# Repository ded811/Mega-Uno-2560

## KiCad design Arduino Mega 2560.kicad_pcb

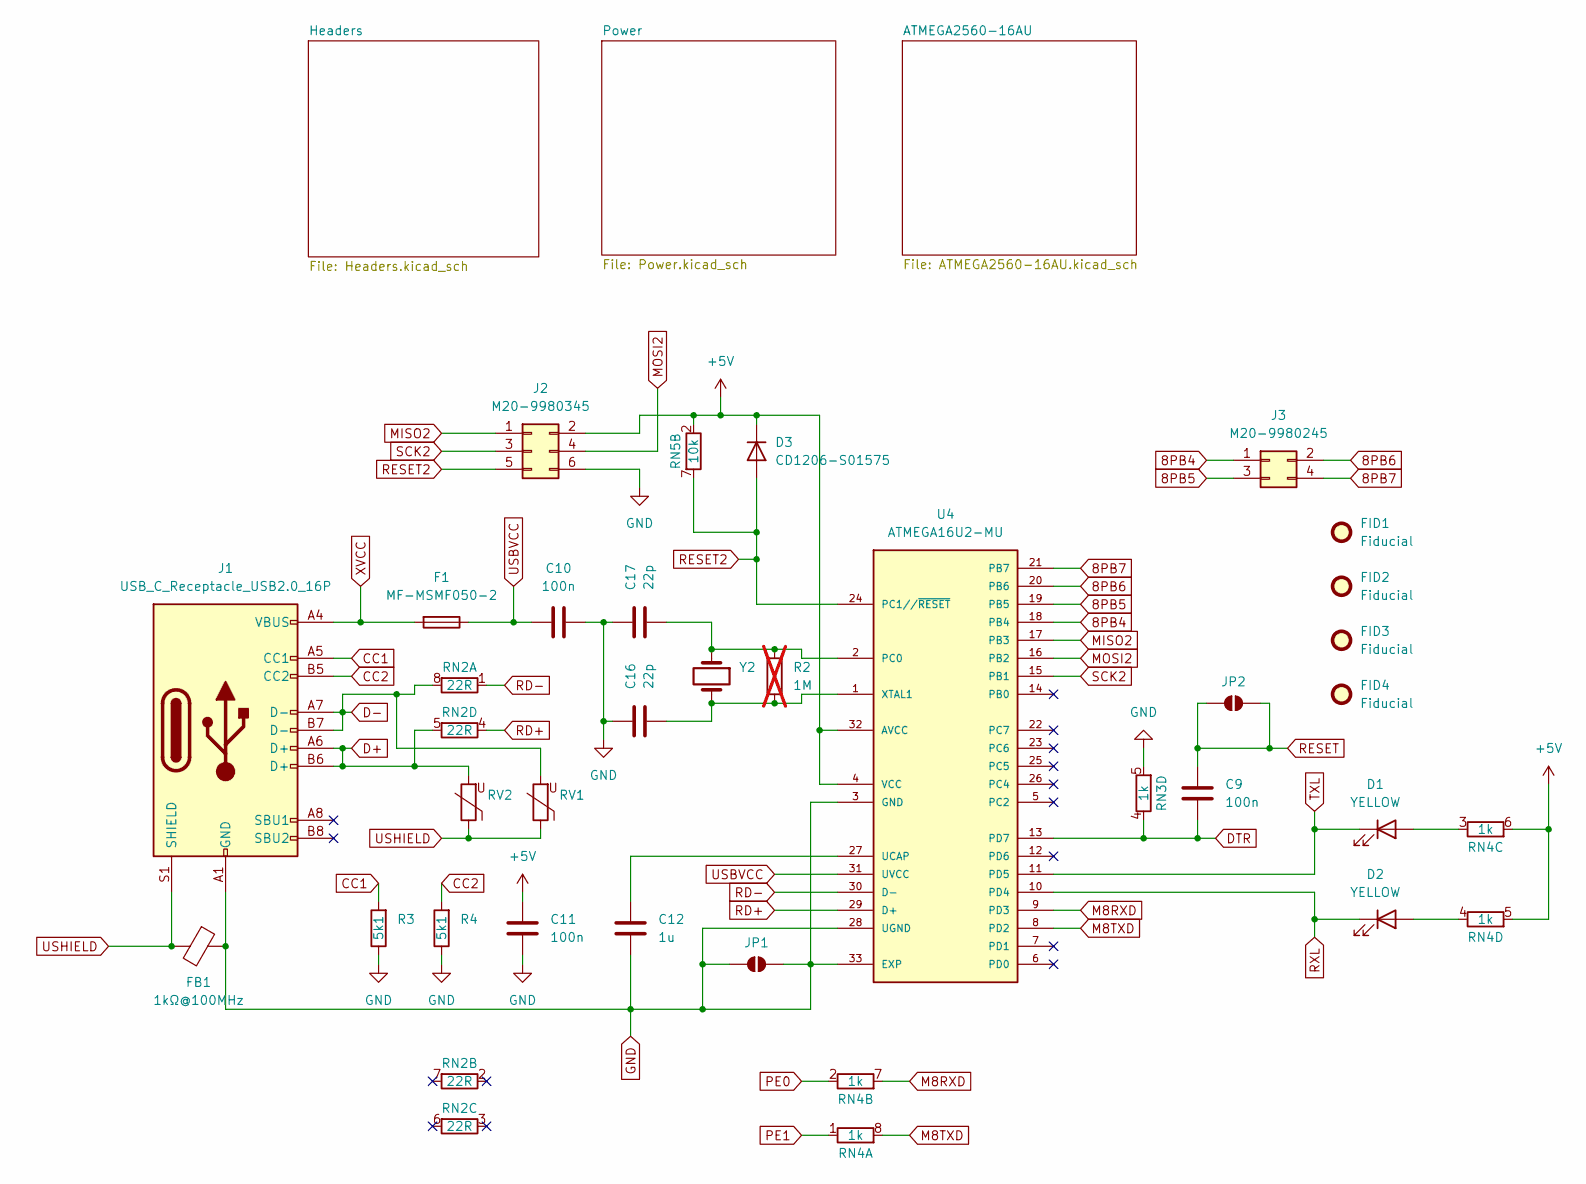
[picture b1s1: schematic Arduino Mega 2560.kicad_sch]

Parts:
C9, C10, C11: 100n; C_0603_1608Metric
C12: 1u; C_0603_1608Metric
C16, C17: 22p; C_0603_1608Metric
D1, D2: YELLOW; LED_0805_2012Metric
D3: CD1206-S01575; D_1206_3216Metric
F1: MF-MSMF050-2; Fuse_1812_4532Metric_Pad1.30x3.40mm_HandSolder
FB1: 1kΩ@100MHz; L_0805_2012Metric
FID1, FID2, FID3, FID4: Fiducial; Fiducial_1mm_Mask3mm
J1: USB_C_Receptacle_USB2.0_16P; USB_C_Receptacle_GCT_USB4105-xx-A_16P_TopMnt_Horizontal
J2: M20-9980345; PinHeader_2x03_P2.54mm_Vertical
J3: M20-9980245; CONN_M20-9980245_HRW
JP1, JP2: SolderJumper_2_Open; SolderJumper-2_P1.3mm_Open_Pad1.0x1.5mm
R2: 1M; R_0603_1608Metric; not fitted
R3, R4: 5k1; R_0603_1608Metric
RN2: 22R; R_Array_Convex_4x0612
RN3, RN4: 1k; R_Array_Convex_4x0612
RN5: 10k; R_Array_Convex_4x0612
RV1, RV2: 5pF@1MHz; R_0603_1608Metric
U4: ATMEGA16U2-MU; VQFN-32-1EP_5x5mm_P0.5mm_EP3.1x3.1mm
Y2: LFXTAL003240BULK; Crystal_HC49-4H_Vertical

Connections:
8PB4: J3.1, U4.18 (PB4)
8PB5: J3.3, U4.19 (PB5)
8PB6: J3.2, U4.20 (PB6)
8PB7: J3.4, U4.21 (PB7)
+5V: C11.1, D3.1 (K), J2.2, RN4.5 (R4.2), RN4.6 (R3.2), RN5.2 (R2.1), U4.4 (VCC), U4.32 (AVCC); also elsewhere on the board
CC1: J1.A5 (CC1), R3.2
CC2: J1.B5 (CC2), R4.2
D+: J1.A6 (D+), J1.B6 (D+), RN2.5 (R4.2), RV2.2
D-: J1.A7 (D-), J1.B7 (D-), RN2.8 (R1.2), RV1.2
DTR: C9.1, RN3.4 (R4.1), U4.13 (PD7)
GND: C10.2, C11.2, C12.2, C16.2, C17.2, FB1.1, J1.A1 (GND), J1.A12 (GND), J1.B1 (GND), J1.B12 (GND), J2.6, JP1.1 (A), JP1.2 (B), R3.1, R4.1, RN3.5 (R4.2), U4.3 (GND), U4.28 (UGND), U4.33 (EXP); also elsewhere on the board
M8RXD: RN4.7 (R2.2), U4.9 (PD3)
M8TXD: RN4.8 (R1.2), U4.8 (PD2)
MISO2: J2.1, U4.17 (PB3)
MOSI2: J2.4, U4.16 (PB2)
unnamed: D1.2 (A), RN4.3 (R3.1)
unnamed: D2.2 (A), RN4.4 (R4.1)
unnamed: C17.1, R2.2, U4.2 (PC0), Y2.1
unnamed: C12.1, U4.27 (UCAP)
unnamed: C16.1, R2.1, U4.1 (XTAL1), Y2.2
PE0: RN4.2 (R2.1); also elsewhere on the board
PE1: RN4.1 (R1.1); also elsewhere on the board
RD+: RN2.4 (R4.1), U4.29 (D+)
RD-: RN2.1 (R1.1), U4.30 (D-)
RESET: C9.2, JP2.1 (A), JP2.2 (B); also elsewhere on the board
RESET2: D3.2 (A), J2.5, RN5.7 (R2.2), U4.24 (PC1//~RESET)
RXL: D2.1 (K), U4.10 (PD4)
SCK2: J2.3, U4.15 (PB1)
TXL: D1.1 (K), U4.11 (PD5)
USBVCC: C10.1, F1.1, U4.31 (UVCC); also elsewhere on the board
USHIELD: FB1.2, J1.S1 (SHIELD), RV1.1, RV2.1
XVCC: F1.2, J1.A4 (VBUS), J1.A9 (VBUS), J1.B4 (VBUS), J1.B9 (VBUS)

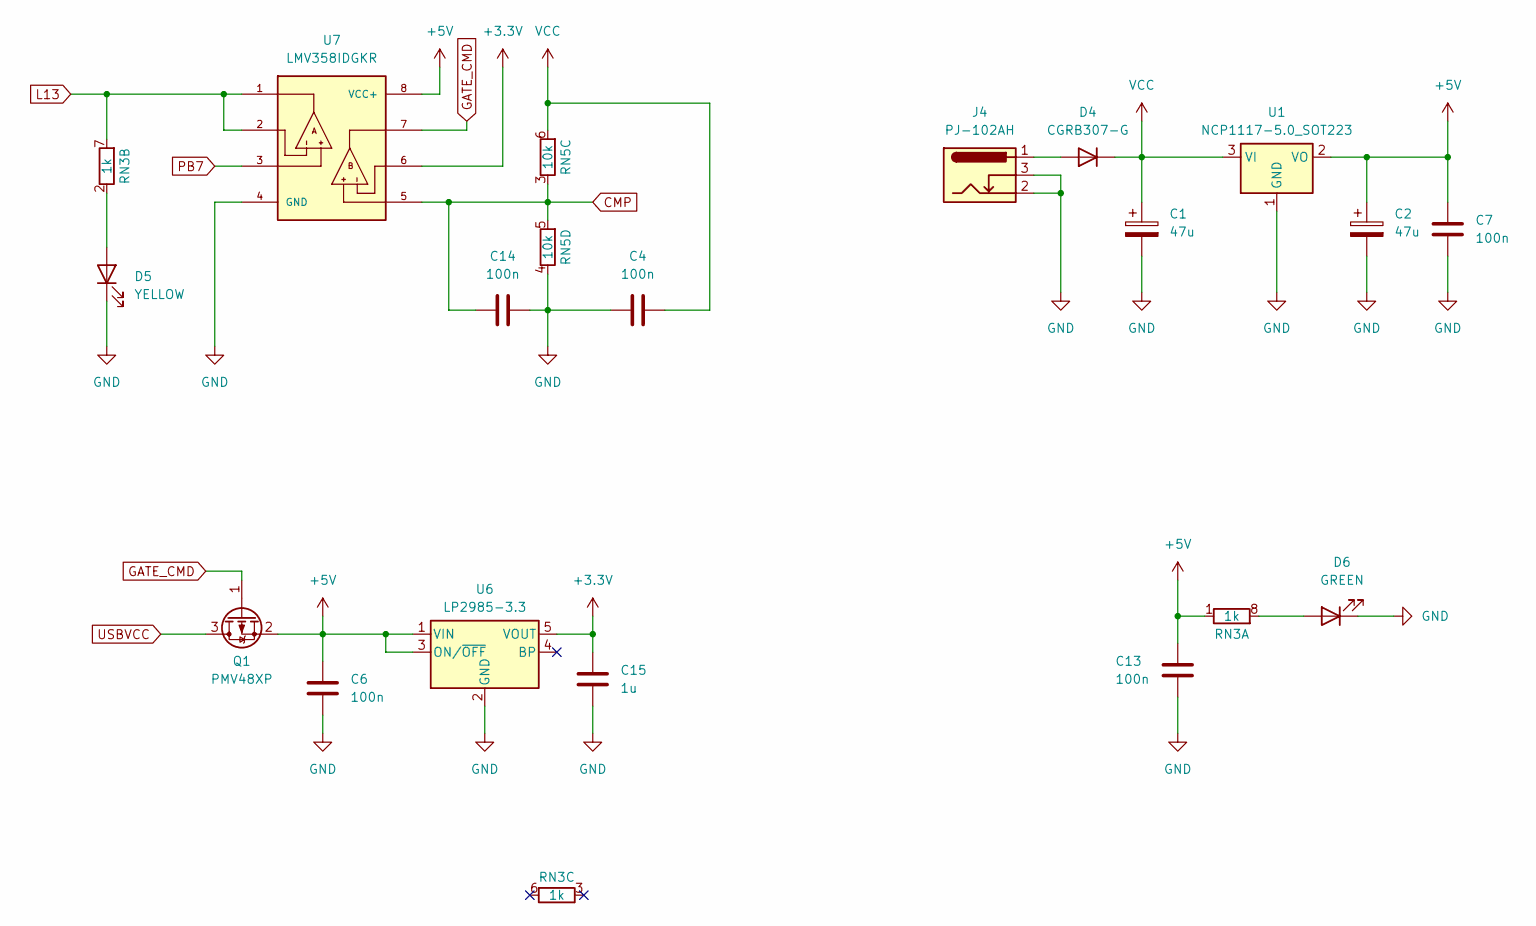
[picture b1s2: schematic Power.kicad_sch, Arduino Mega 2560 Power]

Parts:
C1, C2: 47u; CAP_EEHZA1E470P
C4, C6, C7, C13, C14: 100n; C_0603_1608Metric
C15: 1u; C_0603_1608Metric
D4: CGRB307-G; D_SMB
D5: YELLOW; LED_0805_2012Metric
D6: GREEN; LED_0805_2012Metric
J4: PJ-102AH; BarrelJack_Kycon_KLDX-0202-xC_Horizontal
Q1: PMV48XP; SC-59
RN3: 1k; R_Array_Convex_4x0612
RN5: 10k; R_Array_Convex_4x0612
U1: NCP1117-5.0_SOT223; SOT-223-3_TabPin2
U6: LP2985-3.3; SOT-23-5
U7: LMV358IDGKR; MSOP-8_3x3mm_P0.65mm; PARTREV X

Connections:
+3.3V: C15.2, U6.5 (VOUT), U7.6; also elsewhere on the board
+5V: C2.1, C6.1, C7.1, C13.2, Q1.2 (S), RN3.1 (R1.1), U1.2 (VO), U6.1 (VIN), U6.3 (ON/~OFF), U7.8 (VCC+); also elsewhere on the board
CMP: C14.2, RN5.3 (R3.1), RN5.5 (R4.2), U7.5
GATE_CMD: Q1.1 (G), U7.7
GND: C1.2, C2.2, C4.2, C6.2, C7.2, C13.1, C14.1, C15.1, D5.1 (K), D6.1 (K), J4.2, J4.3, RN5.4 (R4.1), U1.1 (GND), U6.2 (GND), U7.4 (GND); also elsewhere on the board
L13: RN3.7 (R2.2), U7.1, U7.2
unnamed: D4.2 (A), J4.1
unnamed: D5.2 (A), RN3.2 (R2.1)
unnamed: D6.2 (A), RN3.8 (R1.2)
PB7: U7.3; also elsewhere on the board
USBVCC: Q1.3 (D); also elsewhere on the board
VCC: C1.1, C4.1, D4.1 (K), RN5.6 (R3.2), U1.3 (VI); also elsewhere on the board

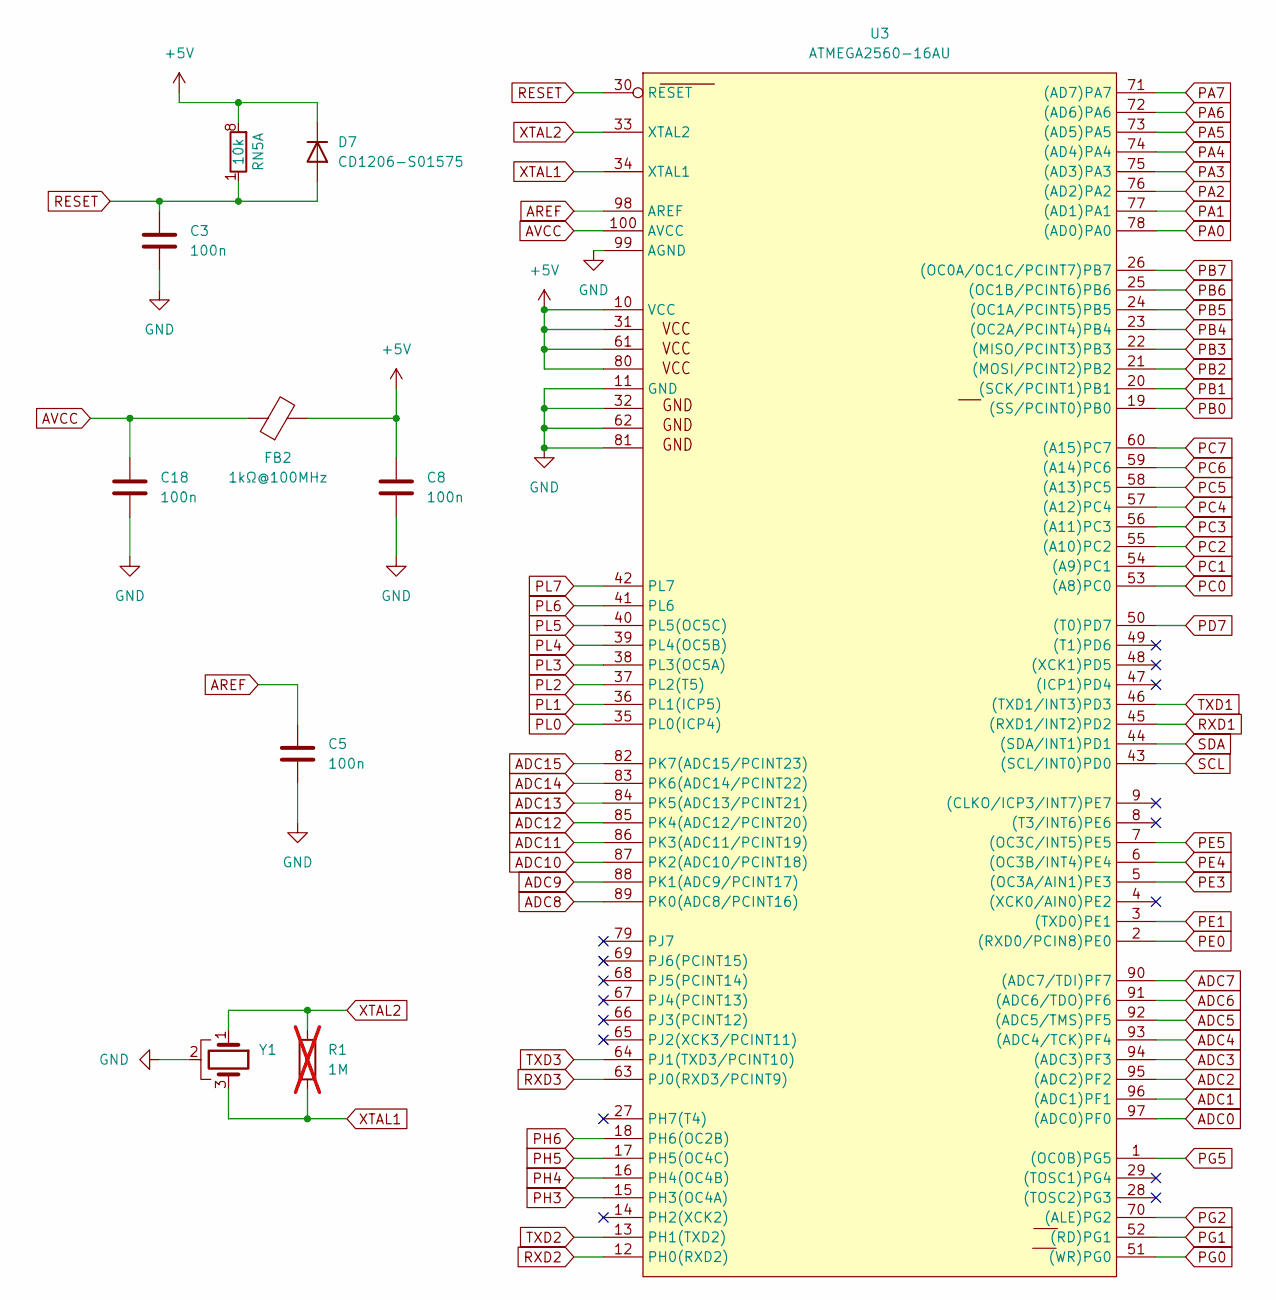
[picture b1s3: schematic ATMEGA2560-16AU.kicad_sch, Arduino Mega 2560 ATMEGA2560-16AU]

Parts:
C3, C5, C8, C18: 100n; C_0603_1608Metric
D7: CD1206-S01575; D_1206_3216Metric
FB2: 1kΩ@100MHz; L_0805_2012Metric
R1: 1M; R_0603_1608Metric; not fitted
RN5: 10k; R_Array_Convex_4x0612
U3: ATMEGA2560-16AU; TQFP-100_14x14mm_P0.5mm
Y1: CSTNE16M0V530000R0; Resonator_SMD_Murata_CSTxExxV-3Pin_3.0x1.1mm

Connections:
+5V: C8.1, D7.1 (K), FB2.2, RN5.8 (R1.2), U3.10 (VCC), U3.31 (VCC1), U3.61 (VCC2), U3.80 (VCC3); also elsewhere on the board
ADC0: U3.97 ((ADC0)PF0); also elsewhere on the board
ADC1: U3.96 ((ADC1)PF1); also elsewhere on the board
ADC2: U3.95 ((ADC2)PF2); also elsewhere on the board
ADC3: U3.94 ((ADC3)PF3); also elsewhere on the board
ADC4: U3.93 ((ADC4/TCK)PF4); also elsewhere on the board
ADC5: U3.92 ((ADC5/TMS)PF5); also elsewhere on the board
ADC6: U3.91 ((ADC6/TDO)PF6); also elsewhere on the board
ADC7: U3.90 ((ADC7/TDI)PF7); also elsewhere on the board
ADC8: U3.89 (PK0(ADC8/PCINT16)); also elsewhere on the board
ADC9: U3.88 (PK1(ADC9/PCINT17)); also elsewhere on the board
ADC10: U3.87 (PK2(ADC10/PCINT18)); also elsewhere on the board
ADC11: U3.86 (PK3(ADC11/PCINT19)); also elsewhere on the board
ADC12: U3.85 (PK4(ADC12/PCINT20)); also elsewhere on the board
ADC13: U3.84 (PK5(ADC13/PCINT21)); also elsewhere on the board
ADC14: U3.83 (PK6(ADC14/PCINT22)); also elsewhere on the board
ADC15: U3.82 (PK7(ADC15/PCINT23)); also elsewhere on the board
AREF: C5.1, U3.98 (AREF); also elsewhere on the board
AVCC: C18.1, FB2.1, U3.100 (AVCC)
GND: C3.2, C5.2, C8.2, C18.2, U3.11 (GND), U3.32 (GND1), U3.62 (GND2), U3.81 (GND3), U3.99 (AGND), Y1.2; also elsewhere on the board
PA0: U3.78 ((AD0)PA0); also elsewhere on the board
PA1: U3.77 ((AD1)PA1); also elsewhere on the board
PA2: U3.76 ((AD2)PA2); also elsewhere on the board
PA3: U3.75 ((AD3)PA3); also elsewhere on the board
PA4: U3.74 ((AD4)PA4); also elsewhere on the board
PA5: U3.73 ((AD5)PA5); also elsewhere on the board
PA6: U3.72 ((AD6)PA6); also elsewhere on the board
PA7: U3.71 ((AD7)PA7); also elsewhere on the board
PB0: U3.19 ((SS/PCINT0)PB0); also elsewhere on the board
PB1: U3.20 ((SCK/PCINT1)PB1); also elsewhere on the board
PB2: U3.21 ((MOSI/PCINT2)PB2); also elsewhere on the board
PB3: U3.22 ((MISO/PCINT3)PB3); also elsewhere on the board
PB4: U3.23 ((OC2A/PCINT4)PB4); also elsewhere on the board
PB5: U3.24 ((OC1A/PCINT5)PB5); also elsewhere on the board
PB6: U3.25 ((OC1B/PCINT6)PB6); also elsewhere on the board
PB7: U3.26 ((OC0A/OC1C/PCINT7)PB7); also elsewhere on the board
PC0: U3.53 ((A8)PC0); also elsewhere on the board
PC1: U3.54 ((A9)PC1); also elsewhere on the board
PC2: U3.55 ((A10)PC2); also elsewhere on the board
PC3: U3.56 ((A11)PC3); also elsewhere on the board
PC4: U3.57 ((A12)PC4); also elsewhere on the board
PC5: U3.58 ((A13)PC5); also elsewhere on the board
PC6: U3.59 ((A14)PC6); also elsewhere on the board
PC7: U3.60 ((A15)PC7); also elsewhere on the board
PD7: U3.50 ((T0)PD7); also elsewhere on the board
PE0: U3.2 ((RXD0/PCIN8)PE0); also elsewhere on the board
PE1: U3.3 ((TXD0)PE1); also elsewhere on the board
PE3: U3.5 ((OC3A/AIN1)PE3); also elsewhere on the board
PE4: U3.6 ((OC3B/INT4)PE4); also elsewhere on the board
PE5: U3.7 ((OC3C/INT5)PE5); also elsewhere on the board
PG0: U3.51 ((WR)PG0); also elsewhere on the board
PG1: U3.52 ((RD)PG1); also elsewhere on the board
PG2: U3.70 ((ALE)PG2); also elsewhere on the board
PG5: U3.1 ((OC0B)PG5); also elsewhere on the board
PH3: U3.15 (PH3(OC4A)); also elsewhere on the board
PH4: U3.16 (PH4(OC4B)); also elsewhere on the board
PH5: U3.17 (PH5(OC4C)); also elsewhere on the board
PH6: U3.18 (PH6(OC2B)); also elsewhere on the board
PL0: U3.35 (PL0(ICP4)); also elsewhere on the board
PL1: U3.36 (PL1(ICP5)); also elsewhere on the board
PL2: U3.37 (PL2(T5)); also elsewhere on the board
PL3: U3.38 (PL3(OC5A)); also elsewhere on the board
PL4: U3.39 (PL4(OC5B)); also elsewhere on the board
PL5: U3.40 (PL5(OC5C)); also elsewhere on the board
PL6: U3.41 (PL6); also elsewhere on the board
PL7: U3.42 (PL7); also elsewhere on the board
RESET: C3.1, D7.2 (A), RN5.1 (R1.1), U3.30 (RESET); also elsewhere on the board
RXD1: U3.45 ((RXD1/INT2)PD2); also elsewhere on the board
RXD2: U3.12 (PH0(RXD2)); also elsewhere on the board
RXD3: U3.63 (PJ0(RXD3/PCINT9)); also elsewhere on the board
SCL: U3.43 ((SCL/INT0)PD0); also elsewhere on the board
SDA: U3.44 ((SDA/INT1)PD1); also elsewhere on the board
TXD1: U3.46 ((TXD1/INT3)PD3); also elsewhere on the board
TXD2: U3.13 (PH1(TXD2)); also elsewhere on the board
TXD3: U3.64 (PJ1(TXD3/PCINT10)); also elsewhere on the board
XTAL1: R1.1, U3.34 (XTAL1), Y1.3
XTAL2: R1.2, U3.33 (XTAL2), Y1.1

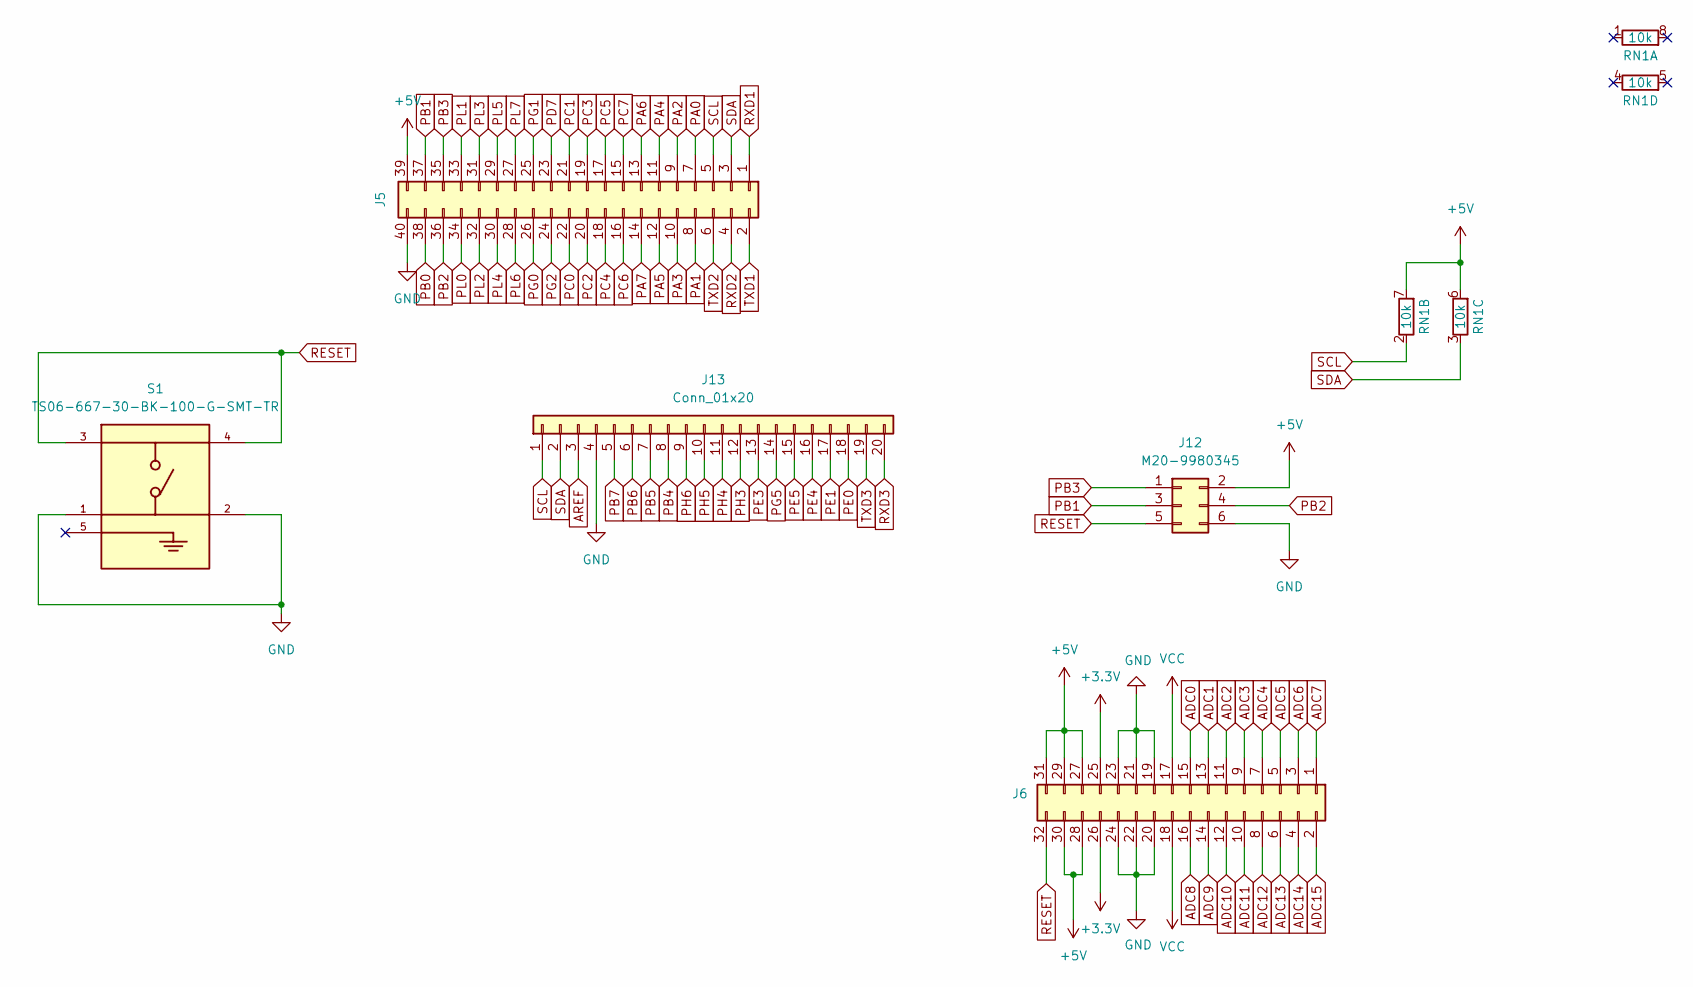
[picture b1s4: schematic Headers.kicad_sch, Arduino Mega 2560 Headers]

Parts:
J5: PPTC182LFBN-RC; PinSocket_2x20_P2.54mm_Vertical
J6: Conn_02x16_Top_Bottom; PinSocket_2x16_P2.54mm_Vertical
J12: M20-9980345; PinHeader_2x03_P2.54mm_Vertical
J13: Conn_01x20; PinSocket_1x20_P2.54mm_Vertical
RN1: 10k; R_Array_Convex_4x0612
S1: TS06-667-30-BK-100-G-SMT-TR; SW_TS06-667-30-BK-100-G-SMT-TR; PARTREV 1.0

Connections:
+3.3V: J6.25, J6.26; also elsewhere on the board
+5V: J5.39, J6.27, J6.28, J6.29, J6.30, J6.31, J12.2, RN1.6 (R3.2), RN1.7 (R2.2); also elsewhere on the board
ADC0: J6.15; also elsewhere on the board
ADC1: J6.13; also elsewhere on the board
ADC2: J6.11; also elsewhere on the board
ADC3: J6.9; also elsewhere on the board
ADC4: J6.7; also elsewhere on the board
ADC5: J6.5; also elsewhere on the board
ADC6: J6.3; also elsewhere on the board
ADC7: J6.1; also elsewhere on the board
ADC8: J6.16; also elsewhere on the board
ADC9: J6.14; also elsewhere on the board
ADC10: J6.12; also elsewhere on the board
ADC11: J6.10; also elsewhere on the board
ADC12: J6.8; also elsewhere on the board
ADC13: J6.6; also elsewhere on the board
ADC14: J6.4; also elsewhere on the board
ADC15: J6.2; also elsewhere on the board
AREF: J13.3; also elsewhere on the board
GND: J5.40, J6.19, J6.20, J6.21, J6.22, J6.23, J6.24, J12.6, J13.4, S1.1, S1.2; also elsewhere on the board
PA0: J5.7; also elsewhere on the board
PA1: J5.8; also elsewhere on the board
PA2: J5.9; also elsewhere on the board
PA3: J5.10; also elsewhere on the board
PA4: J5.11; also elsewhere on the board
PA5: J5.12; also elsewhere on the board
PA6: J5.13; also elsewhere on the board
PA7: J5.14; also elsewhere on the board
PB0: J5.38; also elsewhere on the board
PB1: J5.37, J12.3; also elsewhere on the board
PB2: J5.36, J12.4; also elsewhere on the board
PB3: J5.35, J12.1; also elsewhere on the board
PB4: J13.8; also elsewhere on the board
PB5: J13.7; also elsewhere on the board
PB6: J13.6; also elsewhere on the board
PB7: J13.5; also elsewhere on the board
PC0: J5.22; also elsewhere on the board
PC1: J5.21; also elsewhere on the board
PC2: J5.20; also elsewhere on the board
PC3: J5.19; also elsewhere on the board
PC4: J5.18; also elsewhere on the board
PC5: J5.17; also elsewhere on the board
PC6: J5.16; also elsewhere on the board
PC7: J5.15; also elsewhere on the board
PD7: J5.23; also elsewhere on the board
PE0: J13.18; also elsewhere on the board
PE1: J13.17; also elsewhere on the board
PE3: J13.13; also elsewhere on the board
PE4: J13.16; also elsewhere on the board
PE5: J13.15; also elsewhere on the board
PG0: J5.26; also elsewhere on the board
PG1: J5.25; also elsewhere on the board
PG2: J5.24; also elsewhere on the board
PG5: J13.14; also elsewhere on the board
PH3: J13.12; also elsewhere on the board
PH4: J13.11; also elsewhere on the board
PH5: J13.10; also elsewhere on the board
PH6: J13.9; also elsewhere on the board
PL0: J5.34; also elsewhere on the board
PL1: J5.33; also elsewhere on the board
PL2: J5.32; also elsewhere on the board
PL3: J5.31; also elsewhere on the board
PL4: J5.30; also elsewhere on the board
PL5: J5.29; also elsewhere on the board
PL6: J5.28; also elsewhere on the board
PL7: J5.27; also elsewhere on the board
RESET: J6.32, J12.5, S1.3, S1.4; also elsewhere on the board
RXD1: J5.1; also elsewhere on the board
RXD2: J5.4; also elsewhere on the board
RXD3: J13.20; also elsewhere on the board
SCL: J5.5, J13.1, RN1.2 (R2.1); also elsewhere on the board
SDA: J5.3, J13.2, RN1.3 (R3.1); also elsewhere on the board
TXD1: J5.2; also elsewhere on the board
TXD2: J5.6; also elsewhere on the board
TXD3: J13.19; also elsewhere on the board
VCC: J6.17, J6.18; also elsewhere on the board

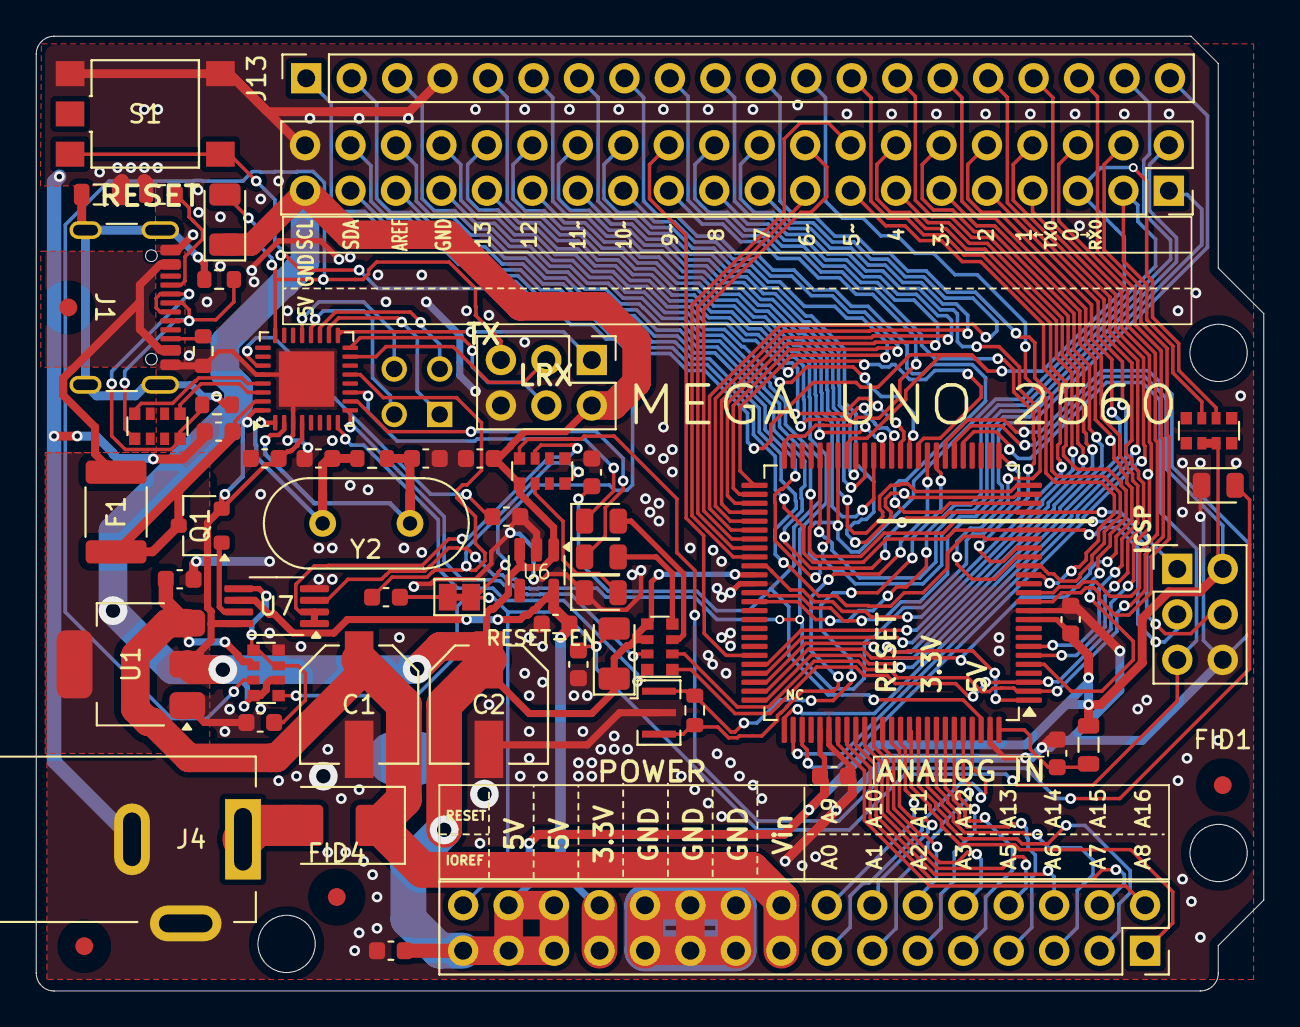
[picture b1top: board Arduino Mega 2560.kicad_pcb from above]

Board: 2 copper layers, 68.6 x 53.3 mm, 62 parts (1 on the bottom side), 112 nets.

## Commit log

2025-11-03 Uploaded WIP files
    all headers routed except some power and reset.
2025-11-03 Continued routing
    All pins except 3.3v are hooked up. Rerouted lots of traces to no longer produce vias in silkscreen area
2025-11-04 WIP, replace bottom headers
    replaced the two bottom headers with one big 2x16 header.
2025-11-04 Continued work
    almost complete
